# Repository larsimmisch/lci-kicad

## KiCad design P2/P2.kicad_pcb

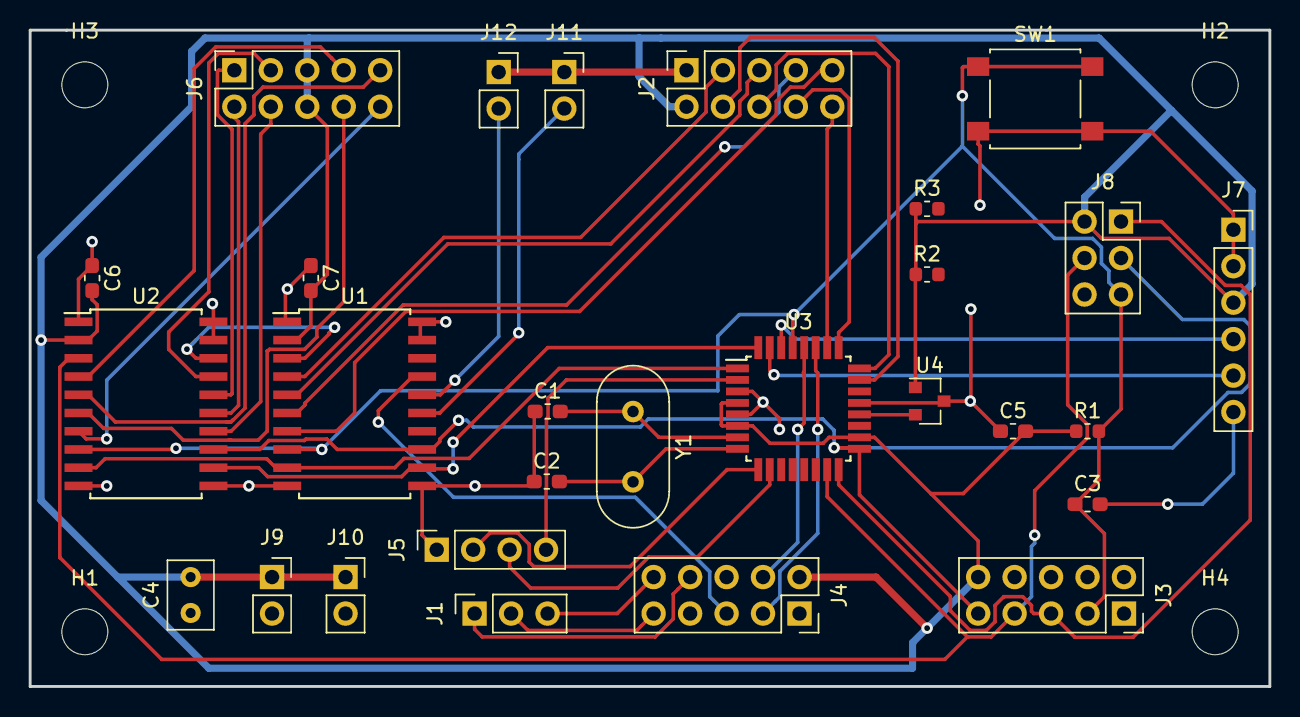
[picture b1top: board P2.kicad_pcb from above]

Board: 2 copper layers, 86.4 x 45.7 mm, 32 parts (0 on the bottom side), 42 nets.

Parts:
C1, C2: 22pF; C_0603_1608Metric_Pad1.05x0.95mm_HandSolder
C3, C5, C6, C7: 100nF; C_0603_1608Metric_Pad1.05x0.95mm_HandSolder
C4: 1u; C_Rect_L4.6mm_W3.0mm_P2.50mm_MKS02_FKP02
H1, H2, H3, H4: MountingHole; MountingHole_3.2mm_M3_ISO14580
J1: 12v; PinSocket_1x03_P2.54mm_Vertical
J2: Channels; PinSocket_2x05_P2.54mm_Vertical
J3: Noritake; PinSocket_2x05_P2.54mm_Vertical
J4: POWER; PinSocket_2x05_P2.54mm_Vertical
J5: Q; PinSocket_1x04_P2.54mm_Vertical
J6: Volume; PinSocket_2x05_P2.54mm_Vertical
J7: PGM; PinSocket_1x06_P2.54mm_Vertical
J8: AVR-ISP-6; PinSocket_2x03_P2.54mm_Vertical
J9: PWR1; PinSocket_1x02_P2.54mm_Vertical
J10: PWR2; PinSocket_1x02_P2.54mm_Vertical
J11: r1; PinSocket_1x02_P2.54mm_Vertical
J12: r2; PinSocket_1x02_P2.54mm_Vertical
R1: 10k; R_0603_1608Metric
R2, R3: 4k7; R_0603_1608Metric
SW1: SW_DIP_x01; SW_SPST_B3S-1000
U1, U2: TPIC6595; SOIC-20W_7.5x12.8mm_P1.27mm
U3: ATmega328-AU; TQFP-32_7x7mm_P0.8mm
U4: MAX6100; SOT-23
Y1: Crystal; Crystal_HC18-U_Vertical

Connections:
+5V: C4.2, C5.2, C6.2, C7.2, J2.2, J3.10, J4.2, J6.5, J6.6, J7.3, J8.2, J9.1, J10.1, R1.1, R2.1, R3.1, U1.2, U2.2, U3.4, U3.6, U3.18, U4.1
/12v: J1.1, J4.8
/#RTS: C3.2, J7.6
/-12v: J1.3, J4.10
/ADC0: J2.4, U3.23
/ADC1: J2.6, U3.24
/ADC2: J2.8, U3.25
/ADC3: J2.10, U3.26
/AGND: J1.2, J4.9
/DRAIN0: J2.3, U1.4
/DRAIN1: J2.5, U1.5
/DRAIN2: J2.7, U1.6
/DRAIN3: J2.9, U1.7
/DRAIN5: J11.2, U1.15
/DRAIN6: J12.2, U1.16
/DRAIN7: J4.5, U1.17
/G: U1.9, U2.9, U3.1
/MISO: J3.5, J8.1, U3.16
/MOSI: J3.7, J8.4, U2.3, U3.15
/OUT0: J6.7, U2.4
/OUT1: J6.9, U2.5
/OUT2: J6.8, U2.6
/OUT3: J6.10, U2.7
/OUT4: J6.4, U2.14
/OUT5: J6.2, U2.15
/OUT6: J6.1, U2.16
/OUT7: J6.3, U2.17
/QE1: J5.2, U3.9
/QE2: J5.3, U3.10
/QEB: J5.4, U3.2
/RCK: U1.12, U2.12, U3.32
/RESET: C3.1, J3.3, J8.5, R1.2, SW1.1, U1.8, U2.8, U3.29
/SCK: J3.9, J8.3, U1.13, U2.13, U3.17
/SCL: J4.4, U3.28
/SDA: J4.3, U3.27
GND: C1.1, C2.1, C4.1, C5.1, C6.1, C7.1, J2.1, J3.6, J4.1, J5.1, J7.1, J7.2, J8.6, J9.2, J10.2, J11.1, J12.1, SW1.2, U1.1, U1.10, U1.11, U1.19, U1.20, U2.1, U2.10, U2.11, U2.19, U2.20, U3.3, U3.5, U3.21, U4.3
unnamed: C1.2, U3.7, Y1.1
unnamed: C2.2, U3.8, Y1.2
unnamed: J7.4, U3.30
unnamed: J7.5, U3.31
unnamed: U1.3, U2.18
unnamed: U3.20, U4.2

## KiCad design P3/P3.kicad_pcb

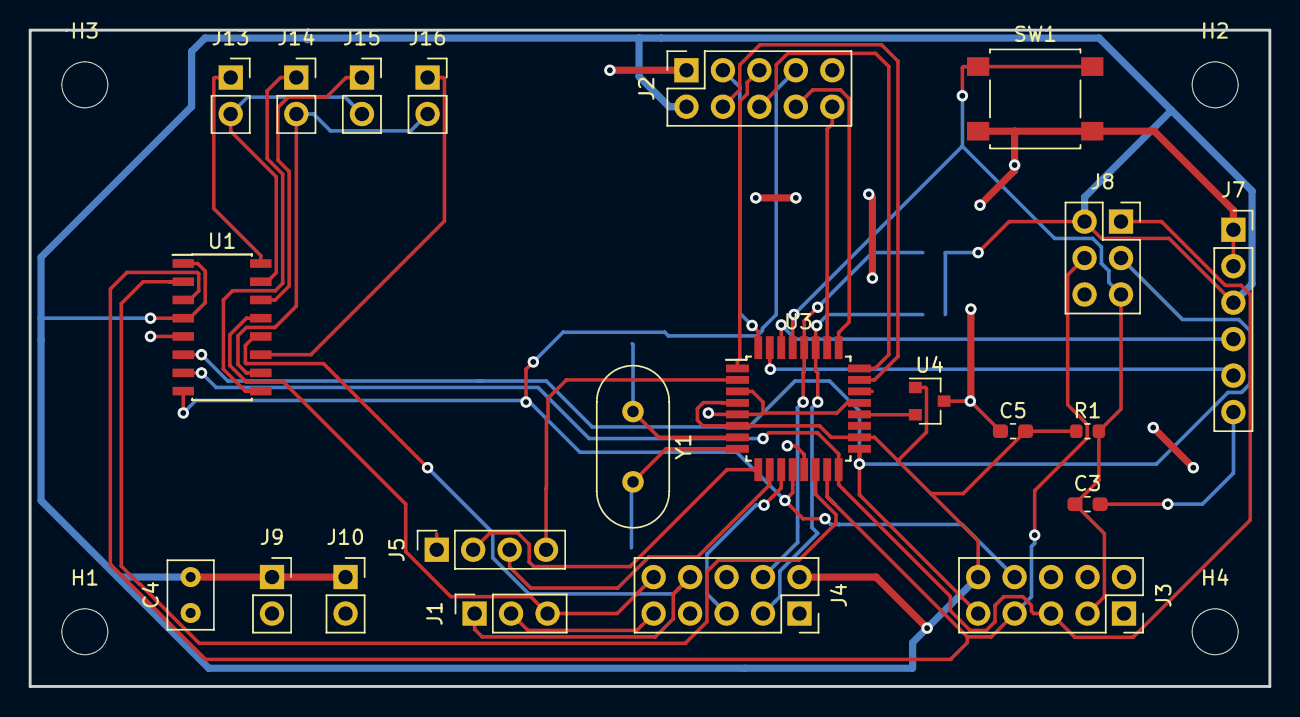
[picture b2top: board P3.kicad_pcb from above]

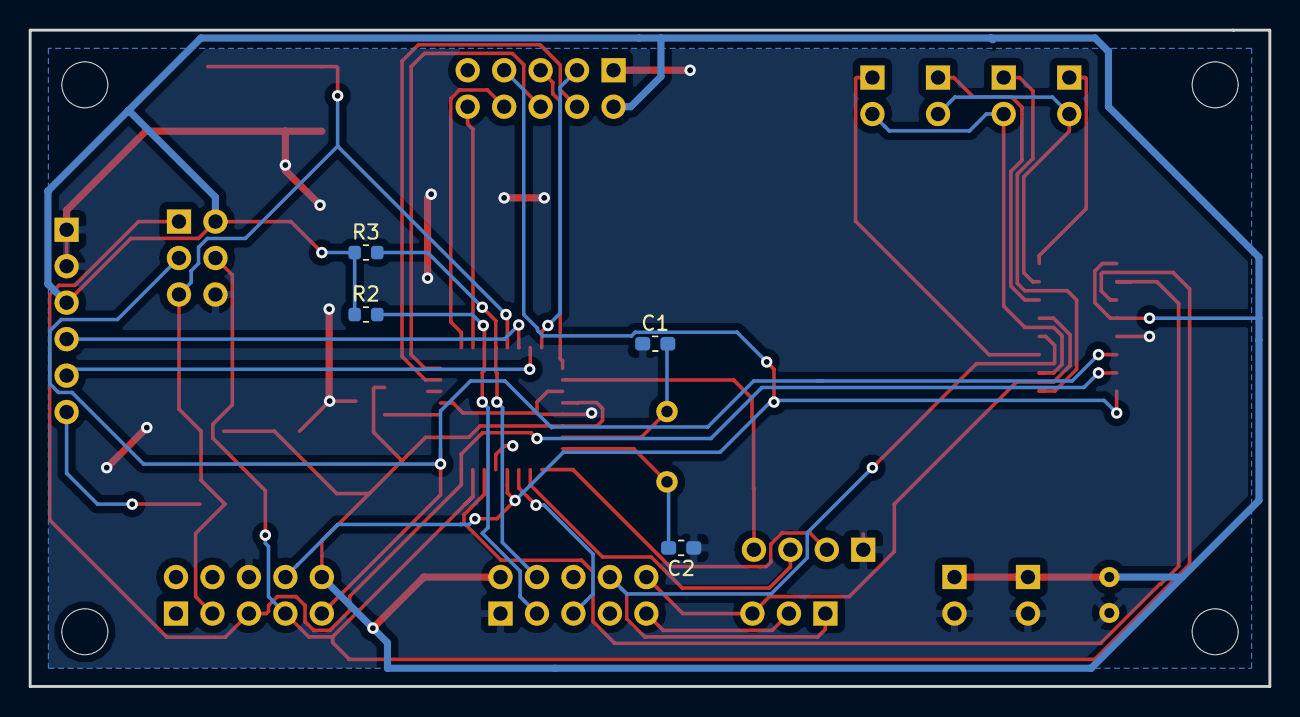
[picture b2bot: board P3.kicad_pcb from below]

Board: 2 copper layers, 86.4 x 45.7 mm, 30 parts (4 on the bottom side), 36 nets.

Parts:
C1, C2: 22pF; C_0603_1608Metric_Pad1.05x0.95mm_HandSolder
C3, C5: 100nF; C_0603_1608Metric_Pad1.05x0.95mm_HandSolder
C4: 1u; C_Rect_L4.6mm_W3.0mm_P2.50mm_MKS02_FKP02
H1, H2, H3, H4: MountingHole; MountingHole_3.2mm_M3_ISO14580
J1: 12v; PinSocket_1x03_P2.54mm_Vertical
J2: Channels; PinSocket_2x05_P2.54mm_Vertical
J3: Noritake; PinSocket_2x05_P2.54mm_Vertical
J4: POWER; PinSocket_2x05_P2.54mm_Vertical
J5: Q; PinSocket_1x04_P2.54mm_Vertical
J7: PGM; PinSocket_1x06_P2.54mm_Vertical
J8: AVR-ISP-6; PinSocket_2x03_P2.54mm_Vertical
J9: PWR1; PinSocket_1x02_P2.54mm_Vertical
J10: PWR2; PinSocket_1x02_P2.54mm_Vertical
J13: inl; PinSocket_1x02_P2.54mm_Vertical
J14: inr; PinSocket_1x02_P2.54mm_Vertical
J15: outl; PinSocket_1x02_P2.54mm_Vertical
J16: outr; PinSocket_1x02_P2.54mm_Vertical
R1: 10k; R_0603_1608Metric
R2, R3: 4k7; R_0603_1608Metric
SW1: SW_DIP_x01; SW_SPST_B3S-1000
U1: PGA2310; SOIC-16_3.9x9.9mm_P1.27mm
U3: ATmega328-AU; TQFP-32_7x7mm_P0.8mm
U4: MAX6100; SOT-23
Y1: Crystal; Crystal_HC18-U_Vertical

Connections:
+5V: C4.2, C5.2, J2.2, J3.10, J4.2, J7.3, J8.2, J9.1, J10.1, R1.1, R2.1, R3.1, U1.1, U1.4, U3.4, U3.6, U3.18, U4.1
/#RTS: C3.2, J7.6
/+12v: J1.1, J4.8, U1.12
/-12v: J1.3, J4.10, U1.13
/ADC0: J2.4, U3.23
/ADC1: J2.6, U3.24
/ADC2: J2.8, U3.25
/ADC3: J2.10, U3.26
/AGND: J1.2, J4.9
/AGNDL: J13.2, J15.2, U1.15
/AGNDR: J14.2, J16.2, U1.10
/INL: J13.1, U1.16
/INR: J14.1, U1.9
/MISO: J3.5, J8.1, U1.7, U3.16
/MOSI: J3.7, J8.4, U1.3, U3.15
/PB0: J2.7, J3.8, U1.8, U3.12
/PB1: J2.9, U3.13
/PD2: J2.3, U3.32
/PD3: J2.5, U3.1
/PD7: J4.5, U3.11
/QE1: J5.2, U3.9
/QE2: J5.3, U3.10
/QEB: J5.4, U3.2
/RESET: C3.1, J3.3, J8.5, R1.2, SW1.1, U3.29
/SCK: J3.9, J8.3, U1.6, U3.17
/SCL: J4.4, R3.2, U3.28
/SDA: J4.3, R2.2, U3.27
/SS: U1.2, U3.14
/VOUTL: J15.1, U1.14
/VOUTR: J16.1, U1.11
GND: C1.1, C2.1, C4.1, C5.1, J2.1, J3.6, J4.1, J5.1, J7.1, J7.2, J8.6, J9.2, J10.2, SW1.2, U1.5, U3.3, U3.5, U3.21, U4.3
unnamed: C1.2, U3.7, Y1.1
unnamed: C2.2, U3.8, Y1.2
unnamed: J7.4, U3.30
unnamed: J7.5, U3.31
unnamed: U3.20, U4.2

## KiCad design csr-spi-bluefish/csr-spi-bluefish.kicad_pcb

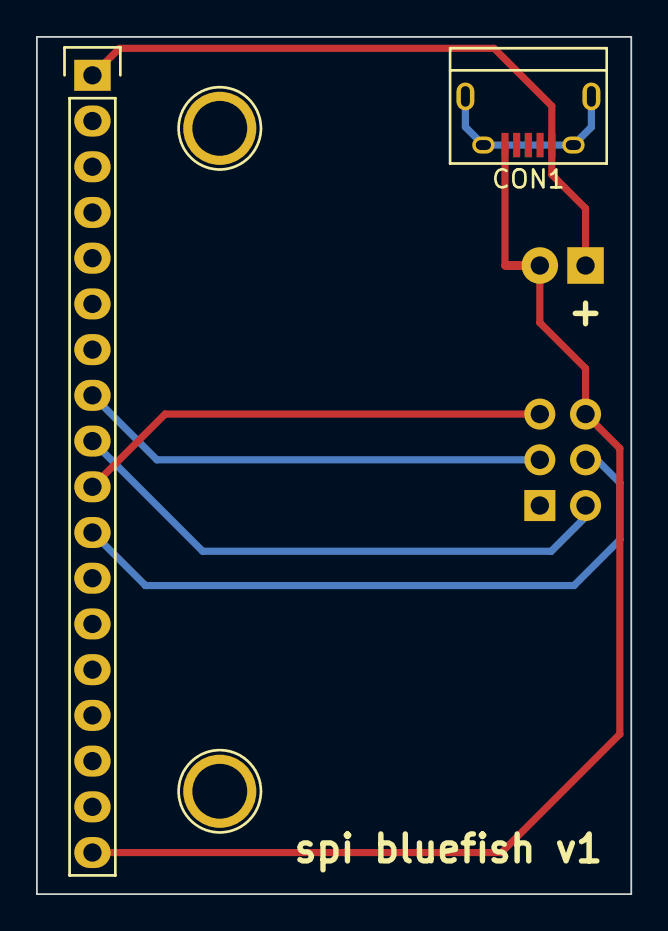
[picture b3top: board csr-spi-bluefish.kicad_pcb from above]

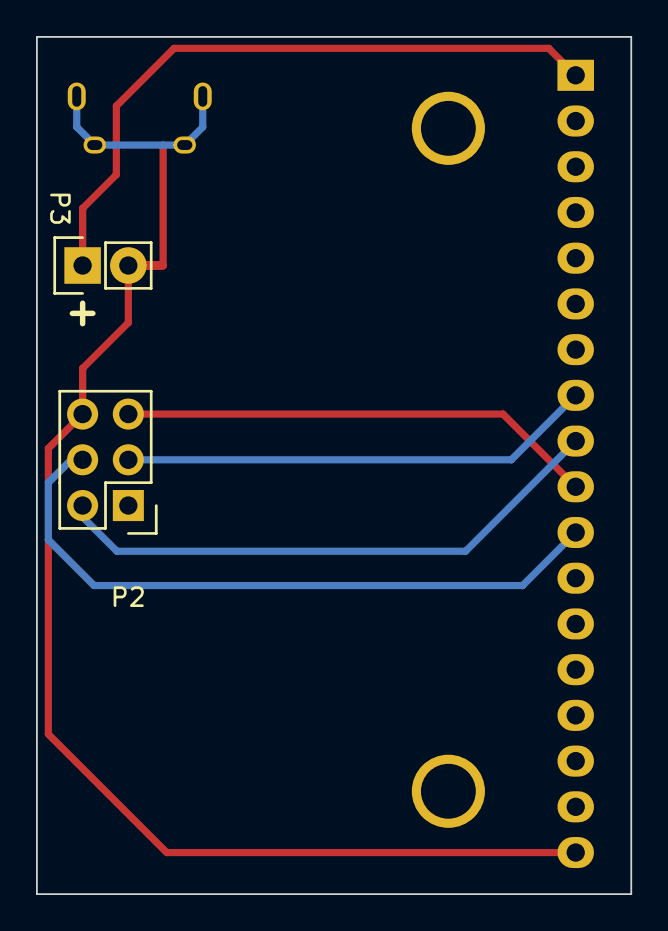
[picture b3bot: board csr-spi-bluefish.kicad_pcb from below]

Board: 2 copper layers, 33.0 x 47.6 mm, 4 parts (2 on the bottom side), 6 nets.

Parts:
CON1: USB-MICRO-B; USB_Micro-B
P1: CONN_01X18; Pin_Header_Straight_1x18
P2: CONN_02X03; Pin_Header_Straight_2x03
P3: CONN_01X02; Pin_Header_Straight_1x02

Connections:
unnamed: P1.11, P2.4
unnamed: CON1.1, P1.1, P3.1
unnamed: CON1.5, P1.18, P2.6, P3.2
unnamed: P1.9, P2.2
unnamed: P1.8, P2.3
unnamed: P1.10, P2.5

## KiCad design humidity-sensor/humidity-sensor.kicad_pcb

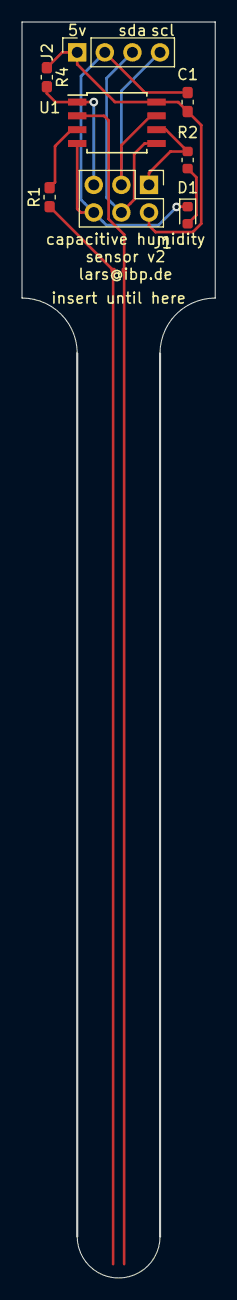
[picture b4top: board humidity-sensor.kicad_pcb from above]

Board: 2 copper layers, 17.8 x 115.6 mm, 9 parts (0 on the bottom side), 10 nets.

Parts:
C1: 100nF; C_0603_1608Metric_Pad1.05x0.95mm_HandSolder
C2: capsensor
D1: LED; LED_0603_1608Metric
J1: AVR-ISP-6; PinHeader_2x03_P2.54mm_Vertical
J2: i2c; PinSocket_1x04_P2.54mm_Vertical
R1: 500k; R_0603_1608Metric_Pad1.05x0.95mm_HandSolder
R2: 1k; R_0603_1608Metric
R4: 10k; R_0603_1608Metric_Pad1.05x0.95mm_HandSolder
U1: ATtiny45-20SU; SOIJ-8_5.3x5.3mm_P1.27mm

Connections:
+5V: C1.1, J1.2, J2.1, R4.1, U1.8
/MISO: J1.1, R2.1, U1.6
/RESET: J1.5, R4.2, U1.1
/SCL: J1.3, J2.4, U1.7
/SDA: J1.4, J2.3, U1.5
GND: C1.2, D1.1, J1.6, J2.2, U1.4
unnamed: C2.1, R1.1
unnamed: C2.2, U1.2
unnamed: D1.2, R2.2
unnamed: R1.2, U1.3

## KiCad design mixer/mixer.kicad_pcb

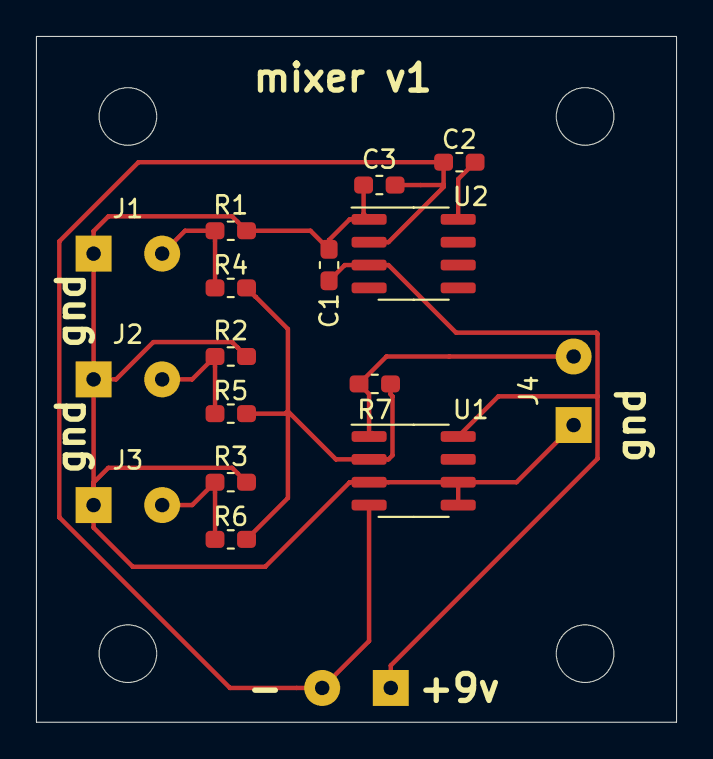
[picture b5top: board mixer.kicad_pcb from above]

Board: 2 copper layers, 35.6 x 38.1 mm, 21 parts (0 on the bottom side), 9 nets.

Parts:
C1, C2, C3: 1u; C_0603_1608Metric_Pad1.05x0.95mm_HandSolder
H1, H2, H3, H4: MountingHole; MountingHole_3.2mm_M3
J1: in0; SolderWirePad_1x02_P3.81mm_Drill0.8mm
J2: in1; SolderWirePad_1x02_P3.81mm_Drill0.8mm
J3: in2; SolderWirePad_1x02_P3.81mm_Drill0.8mm
J4: out; SolderWirePad_1x02_P3.81mm_Drill0.8mm
J5: Conn_01x02; SolderWirePad_1x02_P3.81mm_Drill0.8mm
R1, R2, R3, R4, R5, R6, R7: 10k; R_0603_1608Metric_Pad1.05x0.95mm_HandSolder
U1: OPA2134; SOIC-8_3.9x4.9mm_P1.27mm
U2: TLE2426xD; SOIC-8_3.9x4.9mm_P1.27mm

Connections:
+9V: C1.2, J5.1, U1.8, U2.3
GND: C2.2, C3.2, J5.2, U1.4, U2.2
GNDA: C1.1, C3.1, J1.1, J2.1, J3.1, J4.1, R1.2, R2.2, R3.2, U1.3, U1.5, U1.6, U2.1
unnamed: C2.1, U2.8
unnamed: J1.2, R1.1, R4.2
unnamed: J2.2, R2.1, R5.2
unnamed: J3.2, R3.1, R6.2
unnamed: J4.2, R7.2, U1.1
unnamed: R4.1, R5.1, R6.1, R7.1, U1.2

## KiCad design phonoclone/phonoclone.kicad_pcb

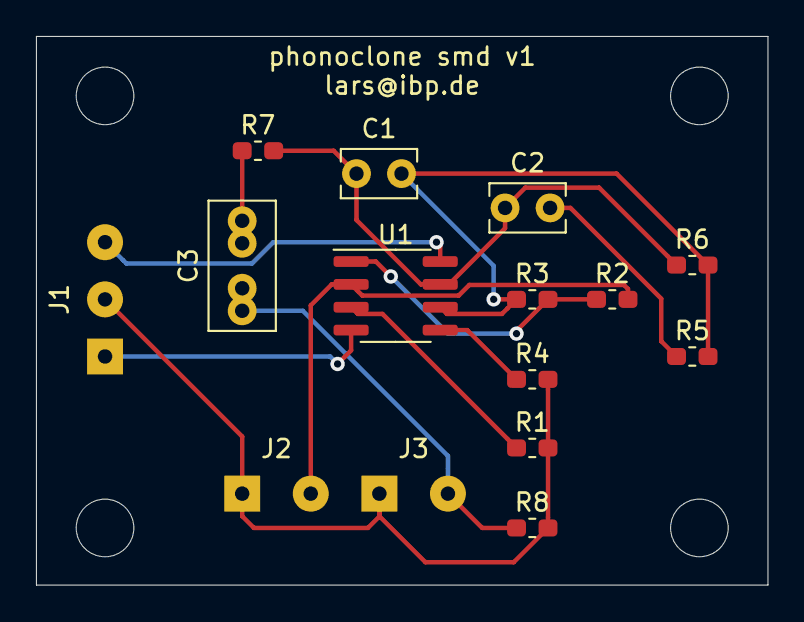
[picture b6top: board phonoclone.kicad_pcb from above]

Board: 2 copper layers, 40.6 x 30.5 mm, 19 parts (0 on the bottom side), 12 nets.

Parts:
C1: 1n; C_Rect_L4.0mm_W2.5mm_P2.50mm
C2: 3n; C_Rect_L4.0mm_W2.5mm_P2.50mm
C3: 2.2u; C_Rect_L7.0mm_W3.5mm_P2.50mm_P5.00mm
H1, H2, H3, H4: MountingHole; MountingHole_3.2mm_M3_DIN965
J1: PWR; SolderWirePad_1x03_P3.175mm_Drill0.8mm
J2: In; SolderWirePad_1x02_P3.81mm_Drill0.8mm
J3: Out; SolderWirePad_1x02_P3.81mm_Drill0.8mm
R1, R7: 47; R_0603_1608Metric_Pad1.05x0.95mm_HandSolder
R2: 1k; R_0603_1608Metric_Pad1.05x0.95mm_HandSolder
R3, R4: 2k2; R_0603_1608Metric_Pad1.05x0.95mm_HandSolder
R5: 110k; R_0603_1608Metric_Pad1.05x0.95mm_HandSolder
R6: 750k; R_0603_1608Metric_Pad1.05x0.95mm_HandSolder
R8: 100; R_0603_1608Metric_Pad1.05x0.95mm_HandSolder
U1: OP275; SOIC-8_3.9x4.9mm_P1.27mm

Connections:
+12V: J1.3, U1.8
-12V: J1.1, U1.4
GND: J1.2, J2.1, J3.1, R1.2, R4.2, R8.2
unnamed: C1.1, C2.1, R6.1, R7.2, U1.7
unnamed: C1.2, R3.1, R5.2, R6.2, U1.6
unnamed: C2.2, R5.1
unnamed: C3.1, J3.2, R8.1
unnamed: C3.2, R7.1
unnamed: J2.2, R2.2, U1.2
unnamed: R1.1, U1.3
unnamed: R2.1, R3.2, U1.1
unnamed: R4.1, U1.5

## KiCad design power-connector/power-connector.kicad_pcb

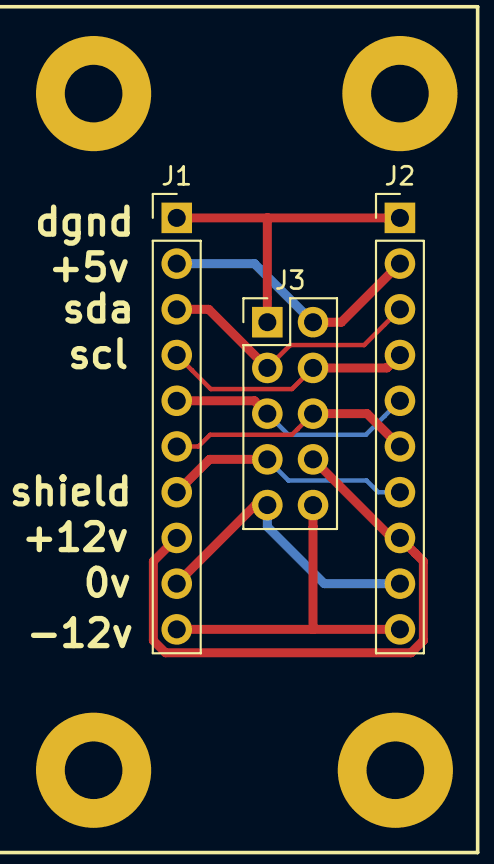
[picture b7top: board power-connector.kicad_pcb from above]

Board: 2 copper layers, 3 parts (0 on the bottom side), 10 nets.

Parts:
J1, J2: Conn_01x10; PinHeader_1x10_P2.54mm_Vertical
J3: Conn_02x05_Odd_Even; PinHeader_2x05_P2.54mm_Vertical

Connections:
unnamed: J1.1, J2.1, J3.1
unnamed: J1.2, J2.2, J3.2
unnamed: J1.3, J2.3, J3.3
unnamed: J1.4, J2.4, J3.4
unnamed: J1.5, J2.5, J3.5
unnamed: J1.6, J2.6, J3.6
unnamed: J1.7, J2.7, J3.7
unnamed: J1.8, J2.8, J3.8
unnamed: J1.9, J2.9, J3.9
unnamed: J1.10, J2.10, J3.10
